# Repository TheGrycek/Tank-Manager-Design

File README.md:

# Tank-Manager

Controller for a gray and a clean water tank, powered from 12 V. An ESP32 measures the tank
levels, the gray water temperature and the tilt of the device, drives the gray water drain valve,
a tank heater and an overfill buzzer, and is operated from a front panel (OLED display and rotary
encoder) or from a phone app over Bluetooth LE.

This repository holds the hardware design and the firmware. The compatible Android app is in
[TheGrycek/Tank-Manager-App](https://github.com/TheGrycek/Tank-Manager-App).

## Folders

| Folder | Contents |
| --- | --- |
| [`esp32/`](esp32/) | MicroPython firmware of the controller |
| [`PCB-design/`](PCB-design/) | KiCad project of the main board |
| [`PCB-front/`](PCB-front/) | KiCad project of the front panel board |
| [`temp_sensor/`](temp_sensor/) | Characterisation of the NTC temperature sensor |
| [`images/`](images/) | Renders of the boards and the enclosure used in this README |

### `esp32/`

The firmware: sensor readout, valve, heater and buzzer control, the display menu, Bluetooth LE
communication with the app and the MPU calibration. The components, pins, Bluetooth
characteristics and the calibration procedure are described in [`esp32/README.md`](esp32/README.md).
The phone side is the Android app [Tank-Manager-App](https://github.com/TheGrycek/Tank-Manager-App).

### `PCB-design/`

KiCad project of the main board (`PCB-design.kicad_sch` on an A3 sheet split into functional
blocks, `PCB-design.kicad_pcb`).

It carries:

- the ESP32 DevKitC module, powered with 5 V into its VIN pin (its own regulator makes the 3.3 V),
- the 12 V input with reverse polarity protection (P-MOSFET Q5), an on/off switch, time-lag fuses
  (F1 500 mA logic, F2 3.15 A heater, F3 200 mA fast valve) and a transient suppressor, and a Pololu
  D24V10F5 5 V step-down regulator mounted upside down (header soldered from the other side,
  footprint `Pololu_D24V10F5_Rev`),
- power MOSFETs with 15 V gate clamps and PC817 optocouplers for the valve and heater outputs,
- the buzzer with a BS170 transistor,
- the resistor dividers, RC filters (4.7 kΩ + 100 nF) and screw terminals for the level sensors
  (5 mm) and the temperature sensor (smaller 3.5 mm terminal, J3),
- the valve switched on the +12 V side: the common (green-yellow) wire on GND, +12 V on the open
  (blue) or close (brown) wire through a P-MOSFET,
- a 10 Ω shunt in the valve return for measuring the motor current (GPIO33),
- a 9-pin JST XH (2.54 mm clone) connector to the front panel (J7).

The board is 116 x 99.5 mm. It is made by hand (no plated holes): a pad has copper only on the
layers its tracks use, through-hole connections are wires soldered on both sides, and tracks reach
the component side only at parts that are easy to solder from the top. KiCad's footprint-library
comparison is switched off in the design rules, because the pads differ from the library on
purpose. The heating foil was measured at 1.8 A at 12.8 V (about 7.1 Ω,
2.0 A at 14.4 V); F2 is sized for that. The valve motor was measured at about 30 mA while moving;
the 10 Ω shunt (300 mV at the ADC) and the fast 200 mA F3 are sized for that.

`Custom_components.pretty/` holds the footprints drawn for this project (ESP32 DevKitC,
MPU-9250, SH1106 OLED, Pololu D24V10F3 and the upside-down D24V10F5); the front panel project uses them too.

### `PCB-front/`

KiCad project of the front panel board (`PCB-front.kicad_sch`, `PCB-front.kicad_pcb`): the
1.3" SH1106 OLED display, the EC12 rotary encoder, the MPU-9250 module, the 9-pin JST XH
connector to the main board (J1; a 9-wire cable with XH plugs at both ends, pins 1:1) and 10 µF + 100 nF decoupling on the 3.3 V supply.

### 3D models and the enclosure

`PCB-design/3d_models/` holds the models of the parts that have none in the KiCad library: the ESP32
DevKit (DOIT, 30 pins), the 1.3" I2C OLED module, the EC12E encoder (shaft 20 mm above the board),
the MPU-9250 module and the switch wires. They are simplified models drawn from the footprints and
from the modules' dimension drawings (the OLED from the LCDWiki MC130VX drawing), as STEP files that
FreeCAD opens for editing. The Pololu regulator uses Pololu's own STEP (from pololu.com, product
2831), turned upside down to match the `Pololu_D24V10F5_Rev` footprint. Check the dimensions against the parts you have.

`mechanical/` has both boards exported with all parts as STEP (`kicad-cli pcb export step`), for
designing the enclosure in FreeCAD. Heights above the board surface: encoder shaft 20.0 mm and OLED
glass 5.2 mm (front panel), Q5 18.8 mm, R17 15.6 mm and the screw terminals 13.8 mm (main board).
Re-export them after changing a board.

### `enclosure/`

3D-printed enclosure: one body with a removable back cover, mounted from behind the plywood
(about 10 mm).

- **Body** (`body.stl`): box 123 x 106.5 mm behind the plywood with a centred nose 72.8 x 66.8 mm on
  its front. The nose goes through a **73.8 x 67.8 mm** hole in the plywood and stands 2 mm proud of
  its front face; the front wall of the box rests on the back of the plywood. The nose holds the front
  board (self-tapping plastic screws into 7 mm standoffs), the display window (bevelled), the encoder shaft
  hole and the cut-out for the main switch.
- **Mounting:** four M3 x 16-25 screws (pan head with a washer) from the front through 3.5 mm holes
  in the plywood (at x = +-55.5 mm, y = +-47.25 mm from the centre of the hole) into bosses in the
  corners of the front wall of the box. Their nuts slide into the bosses from the inside of the box
  (through the open back); the bosses are closed at the back end, so a screw that is too long stops
  there and cannot reach the main board. The plywood screws hold only the body.
- **Back cover** (`back_cover.stl`): the main board is screwed to 5 mm standoffs on it (self-tapping
  plastic screws in blind holes; the cover plate under them stays closed), and
  the cover is held by 4 M3 screws through ears at the back corners of the body. Their nuts slide into
  slots in the outer side of the ears; the holes go right through the ears, so any screw from
  M3 x 10 up fits. The ears blend into the walls of the body and the cover with rounded notches. A
  drop of glue keeps the nuts from falling out while the cover is off.
- The openings for the wires of the screw terminals and for the ESP32 USB socket are slots in the side
  walls, open towards the back edge; fingers on the cover close them behind the wires. The cover comes
  off together with the main board without unscrewing any wire. Give the JST XH cable to the front
  board 15-20 cm, so the cover can be laid aside with the cable connected.
- Total depth 56 mm: 2 mm in front of the plywood, 44 mm behind it. The depth is set by the main switch
  (~30 mm deep) over the fuse holder F1 of the main board.

Parts: main switch KCD1 type (snap-in rocker, cut-out 19.2 x 12.9 mm, the panel is 2 mm thick around
it), 8 M3 nuts, 4 M3 x 16-25 screws with washers for the plywood, 4 M3 x 10 (or longer) screws for the
cover, and 8 self-tapping plastic screws for the two boards: 2.8 mm thread (2.27 mm core, coarse pitch),
7 mm long, head up to 7.8 mm wide, into 2.4 mm pilot holes 6-6.5 mm deep. Insulating TO-220 bushings
(3 mm hole, collar into the board's 3.5 mm mounting holes) under the heads keep the metal off the
boards.

Print the body nose down (the front wall of the box and the cones under the ears need supports); print
the cover flat, standoffs up. Mounting: screw the front board into the nose and fit the switch, fix the
body to the plywood, wire the screw terminals on the main board (their screws face the open side of
the cover), connect the JST XH cable and the switch wires, then screw the cover on. Trim the leads of
Q5 (vertical TO-220) to ~3 mm, it stands over the cover.

`body.step` and `back_cover.step` are the parts for editing in a CAD program, the STL files are ready
for printing; `enclosure.FCStd` opens both parts with the boards in place in FreeCAD.

### `temp_sensor/`

Data and a script used to find the temperature curve of the NTC 10k sensor:

- `ntc10k_nominal.csv`: nominal, minimum and maximum resistance of the thermistor from -40 °C,
- `r-t_curve.csv`: resistance measured on the actual sensor,
- `r-t_curve.py`: fits the Steinhart-Hart coefficients to the nominal data and plots them
  against the measurements. It needs `numpy`, `pandas`, `scipy` and `matplotlib`.

The fitted coefficients are the ones used by `TemperatureSensor` in `esp32/sensors.py`.

## License

MIT, see [`LICENSE`](LICENSE).

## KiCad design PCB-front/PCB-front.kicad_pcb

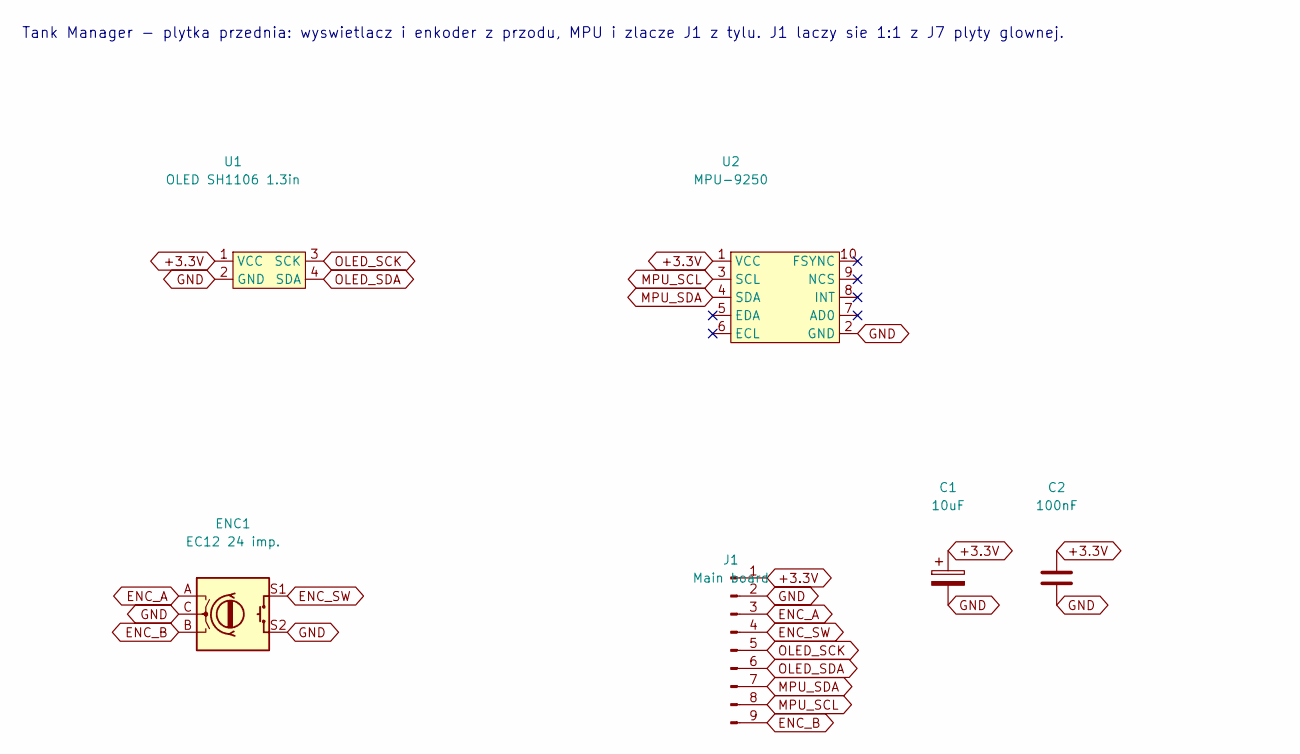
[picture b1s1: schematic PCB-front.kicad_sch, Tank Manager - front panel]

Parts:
C1: 10uF; CP_Radial_D5.0mm_P2.50mm
C2: 100nF; C_Disc_D3.0mm_W1.6mm_P2.50mm
ENC1: EC12 24 imp.; RotaryEncoder_Alps_EC12E-Switch_Vertical_H20mm
J1: Main board; JST_XH_1x09_P2.54mm_Vertical
U1: OLED SH1106 1.3in; OLED_SH1106
U2: MPU-9250; MPU_9250

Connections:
+3.3V: C1.1, C2.1, J1.1, U1.1 (VCC), U2.1 (VCC)
ENC_A: ENC1.A, J1.3
ENC_B: ENC1.B, J1.9
ENC_SW: ENC1.S1, J1.4
GND: C1.2, C2.2, ENC1.C, ENC1.S2, J1.2, U1.2 (GND), U2.2 (GND)
MPU_SCL: J1.8, U2.3 (SCL)
MPU_SDA: J1.7, U2.4 (SDA)
OLED_SCK: J1.5, U1.3 (SCK)
OLED_SDA: J1.6, U1.4 (SDA)

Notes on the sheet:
Tank Manager - plytka przednia: wyswietlacz i enkoder z przodu, MPU i zlacze J1 z tylu. J1 laczy sie 1:1 z J7 plyty glownej.

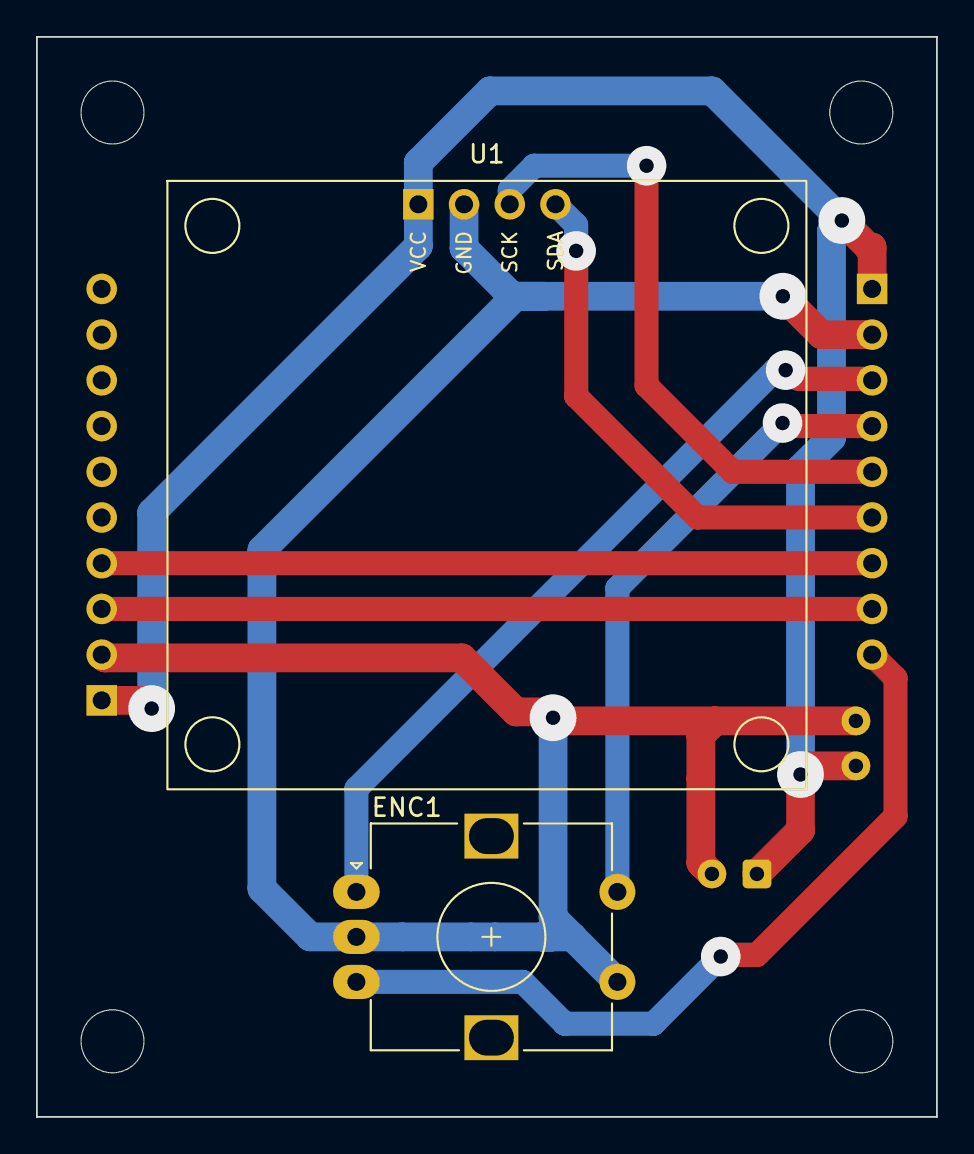
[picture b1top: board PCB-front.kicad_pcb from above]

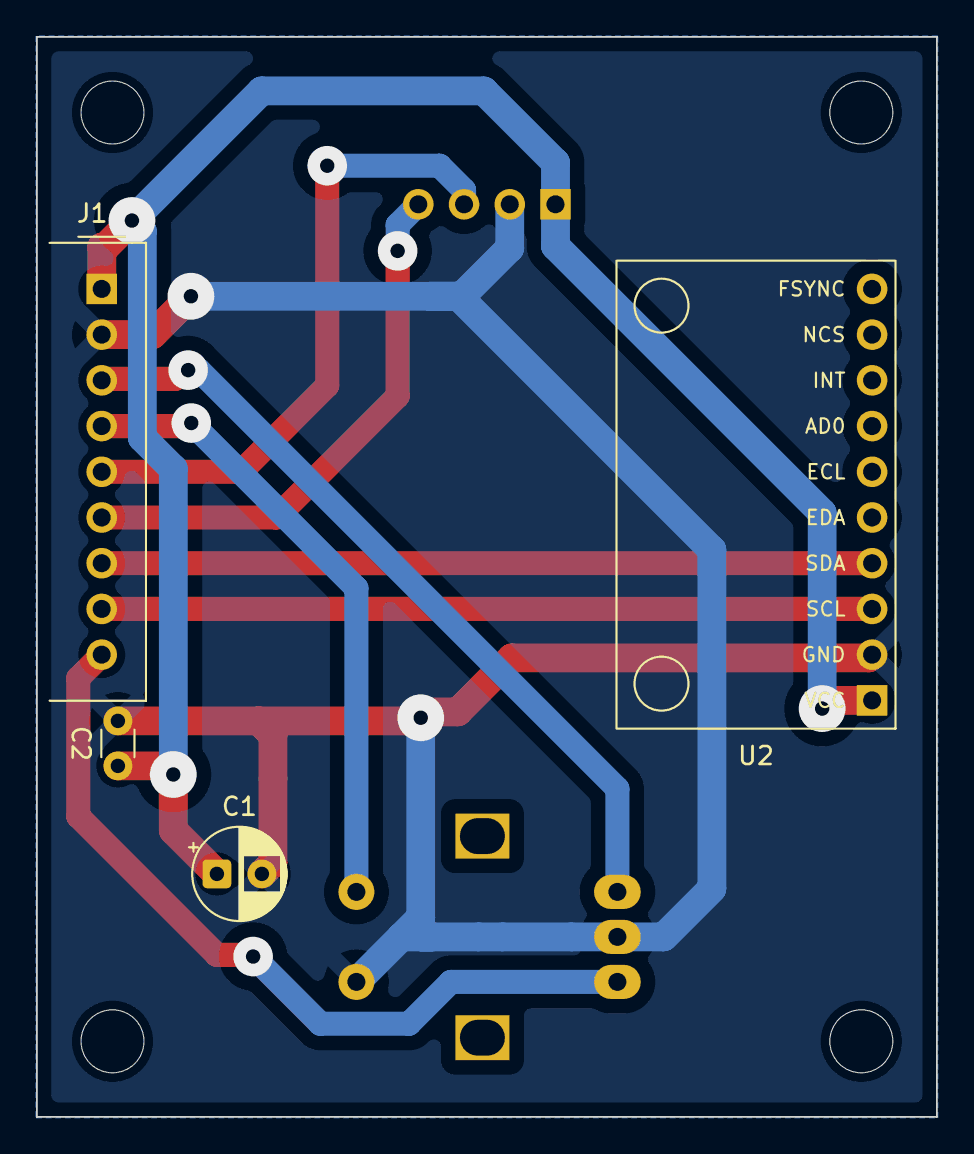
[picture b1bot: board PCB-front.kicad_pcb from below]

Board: 2 copper layers, 50.0 x 60.0 mm, 10 parts (4 on the bottom side), 9 nets.

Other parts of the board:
H1, H2, H3, H4: M3; MountingHole_3.5mm

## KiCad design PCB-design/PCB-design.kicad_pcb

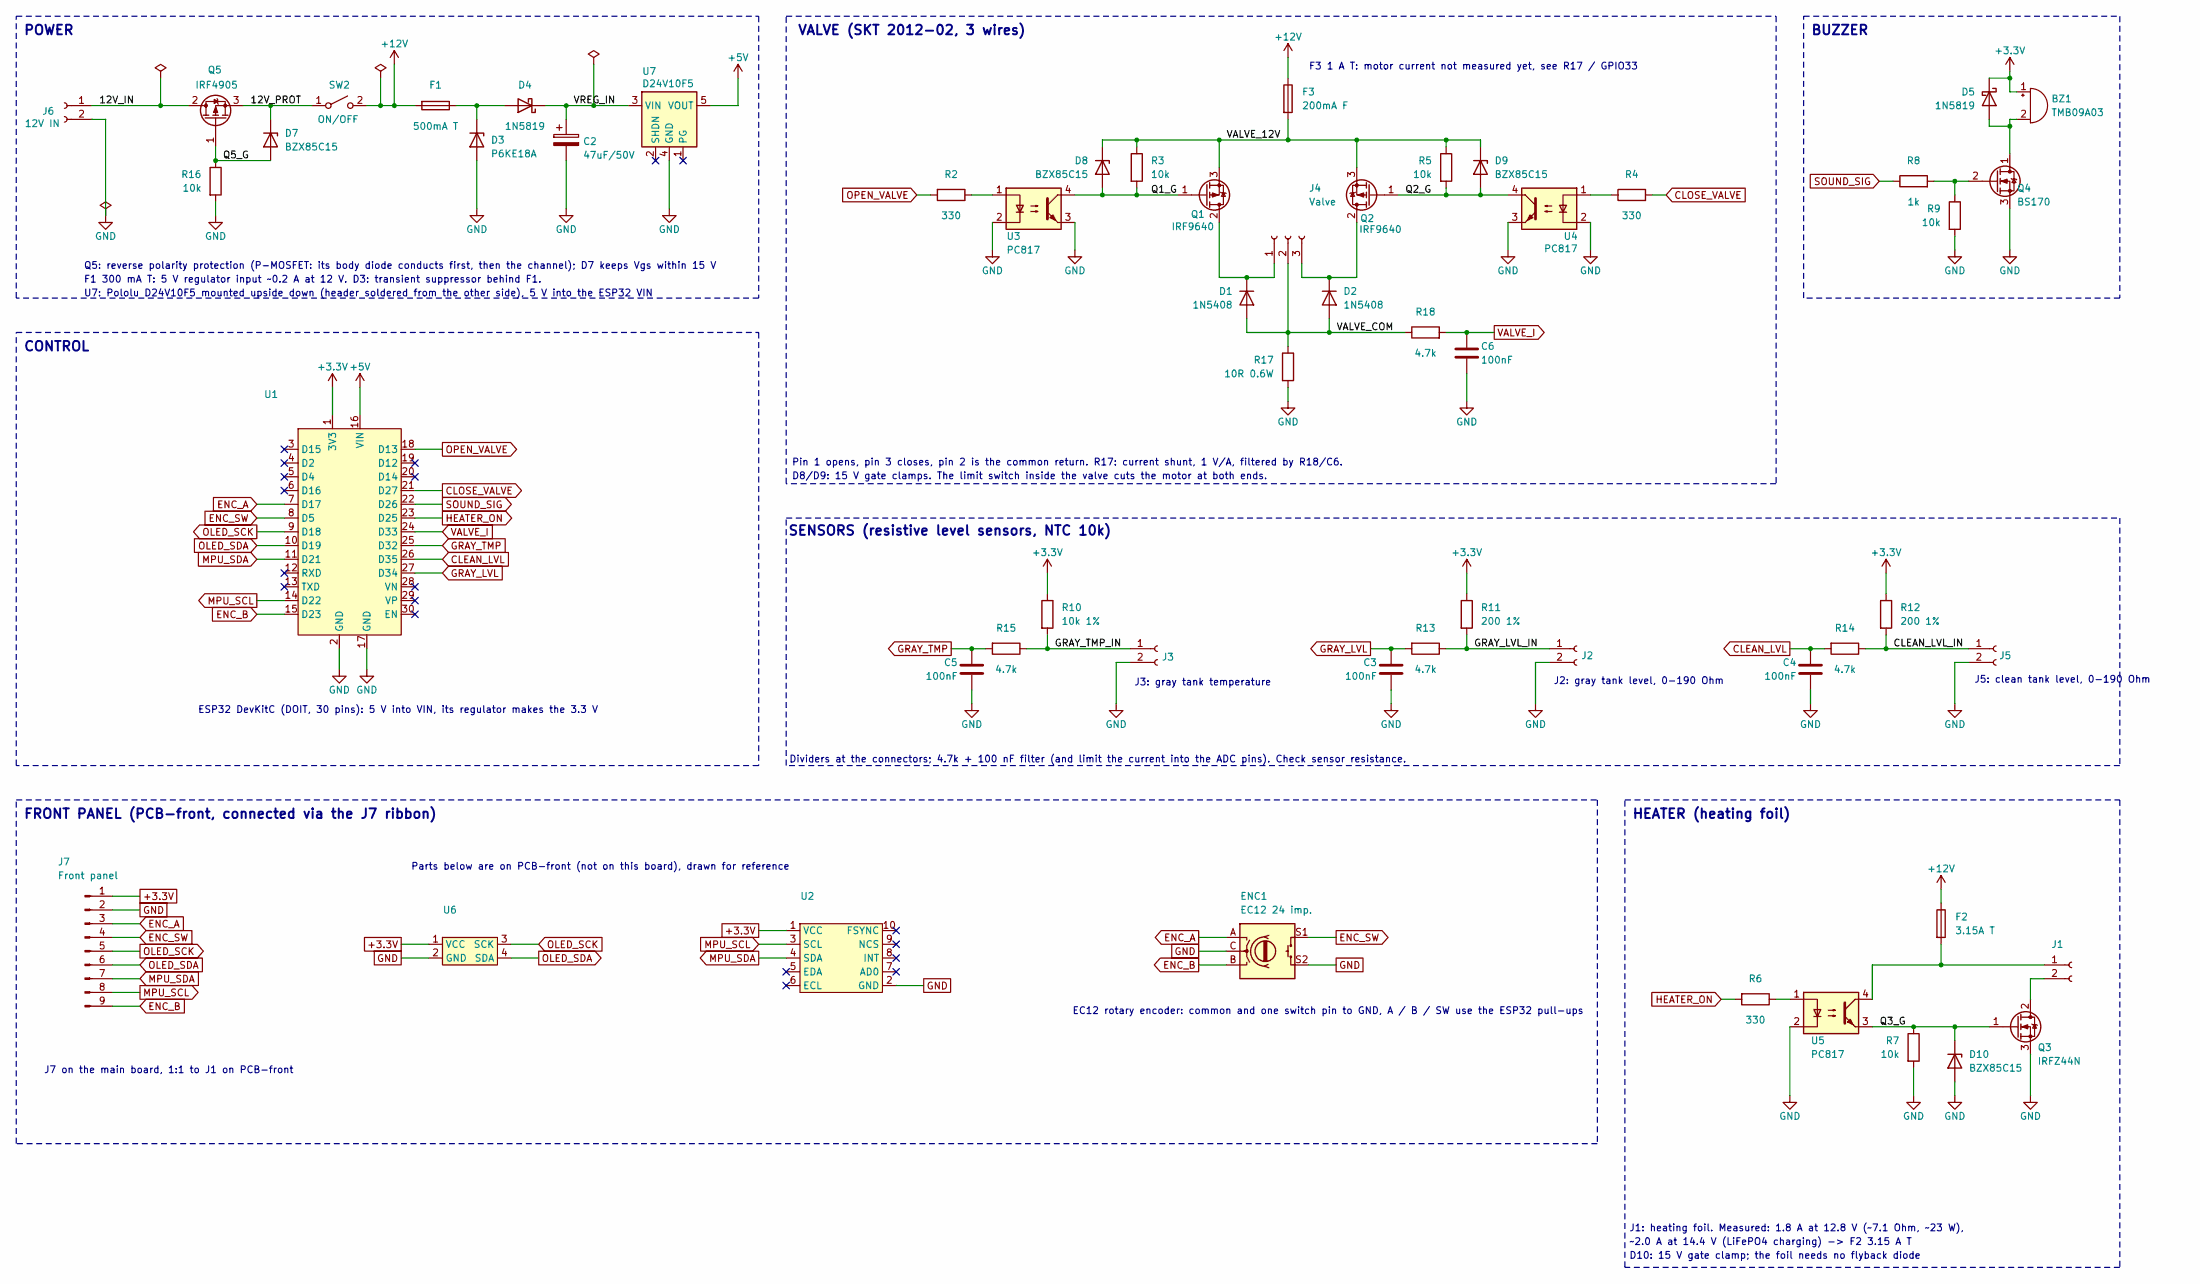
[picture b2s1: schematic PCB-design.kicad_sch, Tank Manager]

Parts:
BZ1: TMB09A03; MagneticBuzzer_CUI_CST-931RP-A
C2: 47uF/50V; CP_Radial_D6.3mm_P2.50mm
C3, C4, C5, C6: 100nF; C_Disc_D3.0mm_W1.6mm_P2.50mm
D1, D2: 1N5408; D_DO-201AD_P15.24mm_Horizontal
D3: P6KE18A; D_DO-15_P10.16mm_Horizontal
D4, D5: 1N5819; D_DO-41_SOD81_P10.16mm_Horizontal
D7, D8, D9, D10: BZX85C15; D_DO-41_SOD81_P5.08mm_Vertical_AnodeUp
ENC1: EC12 24 imp.; RotaryEncoder_Alps_EC12E-Switch_Vertical_H20mm
F1: 500mA T; Fuseholder_Cylinder-5x20mm_Stelvio-Kontek_PTF78_Horizontal_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
F2: 3.15A T; Fuseholder_Cylinder-5x20mm_Stelvio-Kontek_PTF78_Horizontal_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
F3: 200mA F; Fuseholder_Cylinder-5x20mm_Stelvio-Kontek_PTF78_Horizontal_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
J1: Heater; TerminalBlock_Phoenix_MKDS-1,5-2_1x02_P5.00mm_Horizontal
J2: Gray level; TerminalBlock_Phoenix_MKDS-1,5-2_1x02_P5.00mm_Horizontal
J3: Gray temp; TerminalBlock_Phoenix_PT-1,5-2-3.5-H_1x02_P3.50mm_Horizontal
J4: Valve; TerminalBlock_Phoenix_MKDS-1,5-3_1x03_P5.00mm_Horizontal
J5: Clean level; TerminalBlock_Phoenix_MKDS-1,5-2_1x02_P5.00mm_Horizontal
J6: 12V IN; TerminalBlock_Phoenix_MKDS-1,5-2_1x02_P5.00mm_Horizontal
J7: Front panel; JST_XH_1x09_P2.54mm_Vertical
Q1, Q2: IRF9640; TO-220-3_Horizontal_TabDown
Q3: IRFZ44N; TO-220-3_Horizontal_TabDown
Q4: BS170; TO-92_Inline_Wide
Q5: IRF4905; TO-220-3_Vertical
R2, R4, R6: 330; R_Axial_DIN0207_L6.3mm_D2.5mm_P10.16mm_Horizontal
R3, R5, R7, R9: 10k; R_Axial_DIN0207_L6.3mm_D2.5mm_P10.16mm_Horizontal
R8: 1k; R_Axial_DIN0207_L6.3mm_D2.5mm_P10.16mm_Horizontal
R10: 10k 1%; R_Axial_DIN0207_L6.3mm_D2.5mm_P10.16mm_Horizontal
R11, R12: 200 1%; R_Axial_DIN0207_L6.3mm_D2.5mm_P10.16mm_Horizontal
R13, R14, R15, R18: 4.7k; R_Axial_DIN0207_L6.3mm_D2.5mm_P2.54mm_Vertical
R16: 10k; R_Axial_DIN0207_L6.3mm_D2.5mm_P2.54mm_Vertical
R17: 10R 0.6W; R_Axial_DIN0414_L11.9mm_D4.5mm_P5.08mm_Vertical
SW2: ON/OFF; SolderWire-1.5sqmm_1x02_P6mm_D1.7mm_OD3mm
U1: ESP32_DEVKIT_C_DOIT
U2: MPU_9250
U3, U4, U5: PC817; DIP-4_W7.62mm
U6: PinHeader_1x04_P2.54mm_Vertical
U7: D24V10F5; Pololu_D24V10F5_Rev

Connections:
+3.3V: BZ1.1 (+), D5.1 (K), J7.1, R10.1, R11.1, R12.1, U1.1 (3V3), U2.1 (VCC), U6.1 (VCC)
+5V: U1.16 (VIN), U7.5 (VOUT)
+12V: F1.2, F2.1, F3.1, SW2.2 (B)
/12V_IN: J6.1, Q5.2 (D)
/12V_PROT: D7.1 (K), Q5.3 (S), SW2.1 (A)
/CLEAN_LVL_IN: J5.1, R12.2, R14.1
/GRAY_LVL_IN: J2.1, R11.2, R13.1
/GRAY_TMP_IN: J3.1, R10.2, R15.1
/Q1_G: D8.2 (A), Q1.1 (G), R3.2, U3.4
/Q2_G: D9.2 (A), Q2.1 (G), R5.2, U4.4
/Q3_G: D10.1 (K), Q3.1 (G), R7.1, U5.3
/Q5_G: D7.2 (A), Q5.1 (G), R16.1
/VALVE_12V: D8.1 (K), D9.1 (K), F3.2, Q1.3 (S), Q2.3 (S), R3.1, R5.1
/VALVE_COM: D1.2 (A), D2.2 (A), J4.2, R17.1, R18.1
/VREG_IN: C2.1, D4.1 (K), U7.3 (VIN)
CLEAN_LVL: C4.1, R14.2, U1.26 (D35)
CLOSE_VALVE: R4.2, U1.21 (D27)
ENC_A: ENC1.A, J7.3, U1.7 (D17)
ENC_B: ENC1.B, J7.9, U1.15 (D23)
ENC_SW: ENC1.S1, J7.4, U1.8 (D5)
GND: C2.2, C3.2, C4.2, C5.2, C6.2, D3.2 (A), D10.2 (A), ENC1.C, ENC1.S2, J2.2, J3.2, J5.2, J6.2, J7.2, Q3.3 (S), Q4.3 (S), R7.2, R9.2, R16.2, R17.2, U1.2 (GND), U1.17 (GND), U2.2 (GND), U3.2, U3.3, U4.2, U4.3, U5.2, U6.2 (GND), U7.4 (GND)
GRAY_LVL: C3.1, R13.2, U1.27 (D34)
GRAY_TMP: C5.1, R15.2, U1.25 (D32)
HEATER_ON: R6.2, U1.23 (D25)
MPU_SCL: J7.8, U1.14 (D22), U2.3 (SCL)
MPU_SDA: J7.7, U1.11 (D21), U2.4 (SDA)
unnamed: BZ1.2 (-), D5.2 (A), Q4.1 (D)
unnamed: D1.1 (K), J4.1, Q1.2 (D)
unnamed: D2.1 (K), J4.3, Q2.2 (D)
unnamed: D3.1 (K), D4.2 (A), F1.1
unnamed: F2.2, J1.1, U5.4
unnamed: J1.2, Q3.2 (D)
unnamed: Q4.2 (G), R8.2, R9.1
unnamed: R2.1, U3.1
unnamed: R4.1, U4.1
unnamed: R6.1, U5.1
OLED_SCK: J7.5, U1.9 (D18), U6.3 (SCK)
OLED_SDA: J7.6, U1.10 (D19), U6.4 (SDA)
OPEN_VALVE: R2.2, U1.18 (D13)
SOUND_SIG: R8.1, U1.22 (D26)
VALVE_I: C6.1, R18.2, U1.24 (D33)

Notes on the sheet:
ESP32 DevKitC (DOIT, 30 pins): 5 V into VIN, its regulator makes the 3.3 V
FRONT PANEL (PCB-front, connected via the J7 ribbon)
J5: clean tank level, 0-190 Ohm
J7 on the main board, 1:1 to J1 on PCB-front
HEATER (heating foil)
J3: gray tank temperature
D8/D9: 15 V gate clamps. The limit switch inside the valve cuts the motor at both ends.
Parts below are on PCB-front (not on this board), drawn for reference
J1: heating foil. Measured: 1.8 A at 12.8 V (~7.1 Ohm, ~23 W),
Pin 1 opens, pin 3 closes, pin 2 is the common return. R17: current shunt, 1 V/A, filtered by R18/C6.
POWER
U7: Pololu D24V10F5 mounted upside down (header soldered from the other side), 5 V into the ESP32 VIN
BUZZER
VALVE (SKT 2012-02, 3 wires)
J2: gray tank level, 0-190 Ohm
Dividers at the connectors; 4.7k + 100 nF filter (and limit the current into the ADC pins). Check sensor resistance.
F3 1 A T: motor current not measured yet, see R17 / GPIO33
Q5: reverse polarity protection (P-MOSFET: its body diode conducts first, then the channel); D7 keeps Vgs within 15 V
SENSORS (resistive level sensors, NTC 10k)
CONTROL
~2.0 A at 14.4 V (LiFePO4 charging) -> F2 3.15 A T
F1 300 mA T: 5 V regulator input ~0.2 A at 12 V. D3: transient suppressor behind F1.
EC12 rotary encoder: common and one switch pin to GND, A / B / SW use the ESP32 pull-ups
D10: 15 V gate clamp; the foil needs no flyback diode

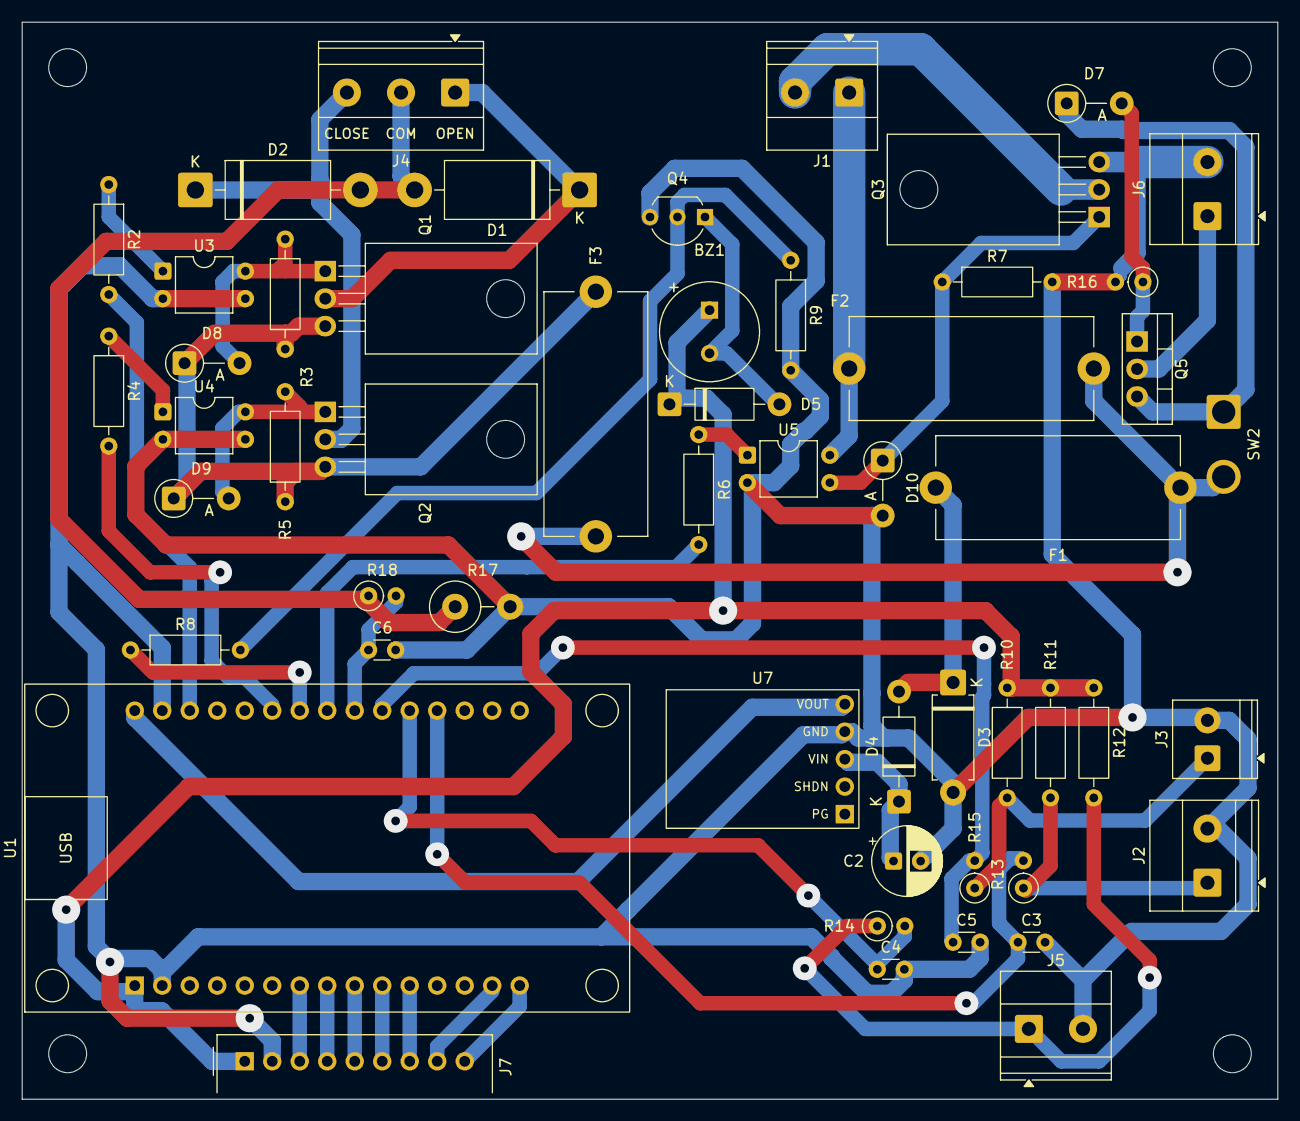
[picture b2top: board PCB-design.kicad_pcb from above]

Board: 2 copper layers, 116.0 x 99.5 mm, 57 parts (0 on the bottom side), 41 nets.

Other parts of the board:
H1, H2, H3, H4: M3; MountingHole_3.5mm

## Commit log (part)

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2025-12-26 esp32 code initialized
2025-12-26 temp sensor data added
2025-12-26 PCB design init
2026-01-11 Buzzer added, extra valve states
